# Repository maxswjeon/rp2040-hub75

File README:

# RP2040 HUB75 Panel Library

This is a HUB75 Panel Library, with PIO and DMA support and Virtual Screen with Chainning

## Virtual Screen

> **Info**
>
> Currently, constructing panels with different sizes are not supported yet.

### Configuration

Virtual Screen is constructed with same `Panel` class. The constructor should be called with those informations.

- Physical Panel Width
- Physical Panel Height
- Physical Panel Count
- `PanelConfig` array

**Important**
The order of the `PanelConfig` info should follow the wire, from the closest to the RP2040 to the end.

#### Examples

**Example 1**

```
------------------------      ------------------------
|                      |      |                      |
|                      | ---- |                      |
|                    . |      |                    . |
------------------------      ------------------------
            |
------------------------      ------------------------
| .                    |      | .                    |
|                      | ---- |                      | ---
|                      |      |                      |
------------------------      ------------------------
```

```json
[
  {
    "rotation": 0,
    "next_position": "LEFT"
  },
  {
    "rotation": 0,
    "next_position": "UP"
  },
  {
    "rotation": 180,
    "next_position": "RIGHT"
  },
  {
    "rotation": 180,
    "next_position": "NONE"
  }
]
```

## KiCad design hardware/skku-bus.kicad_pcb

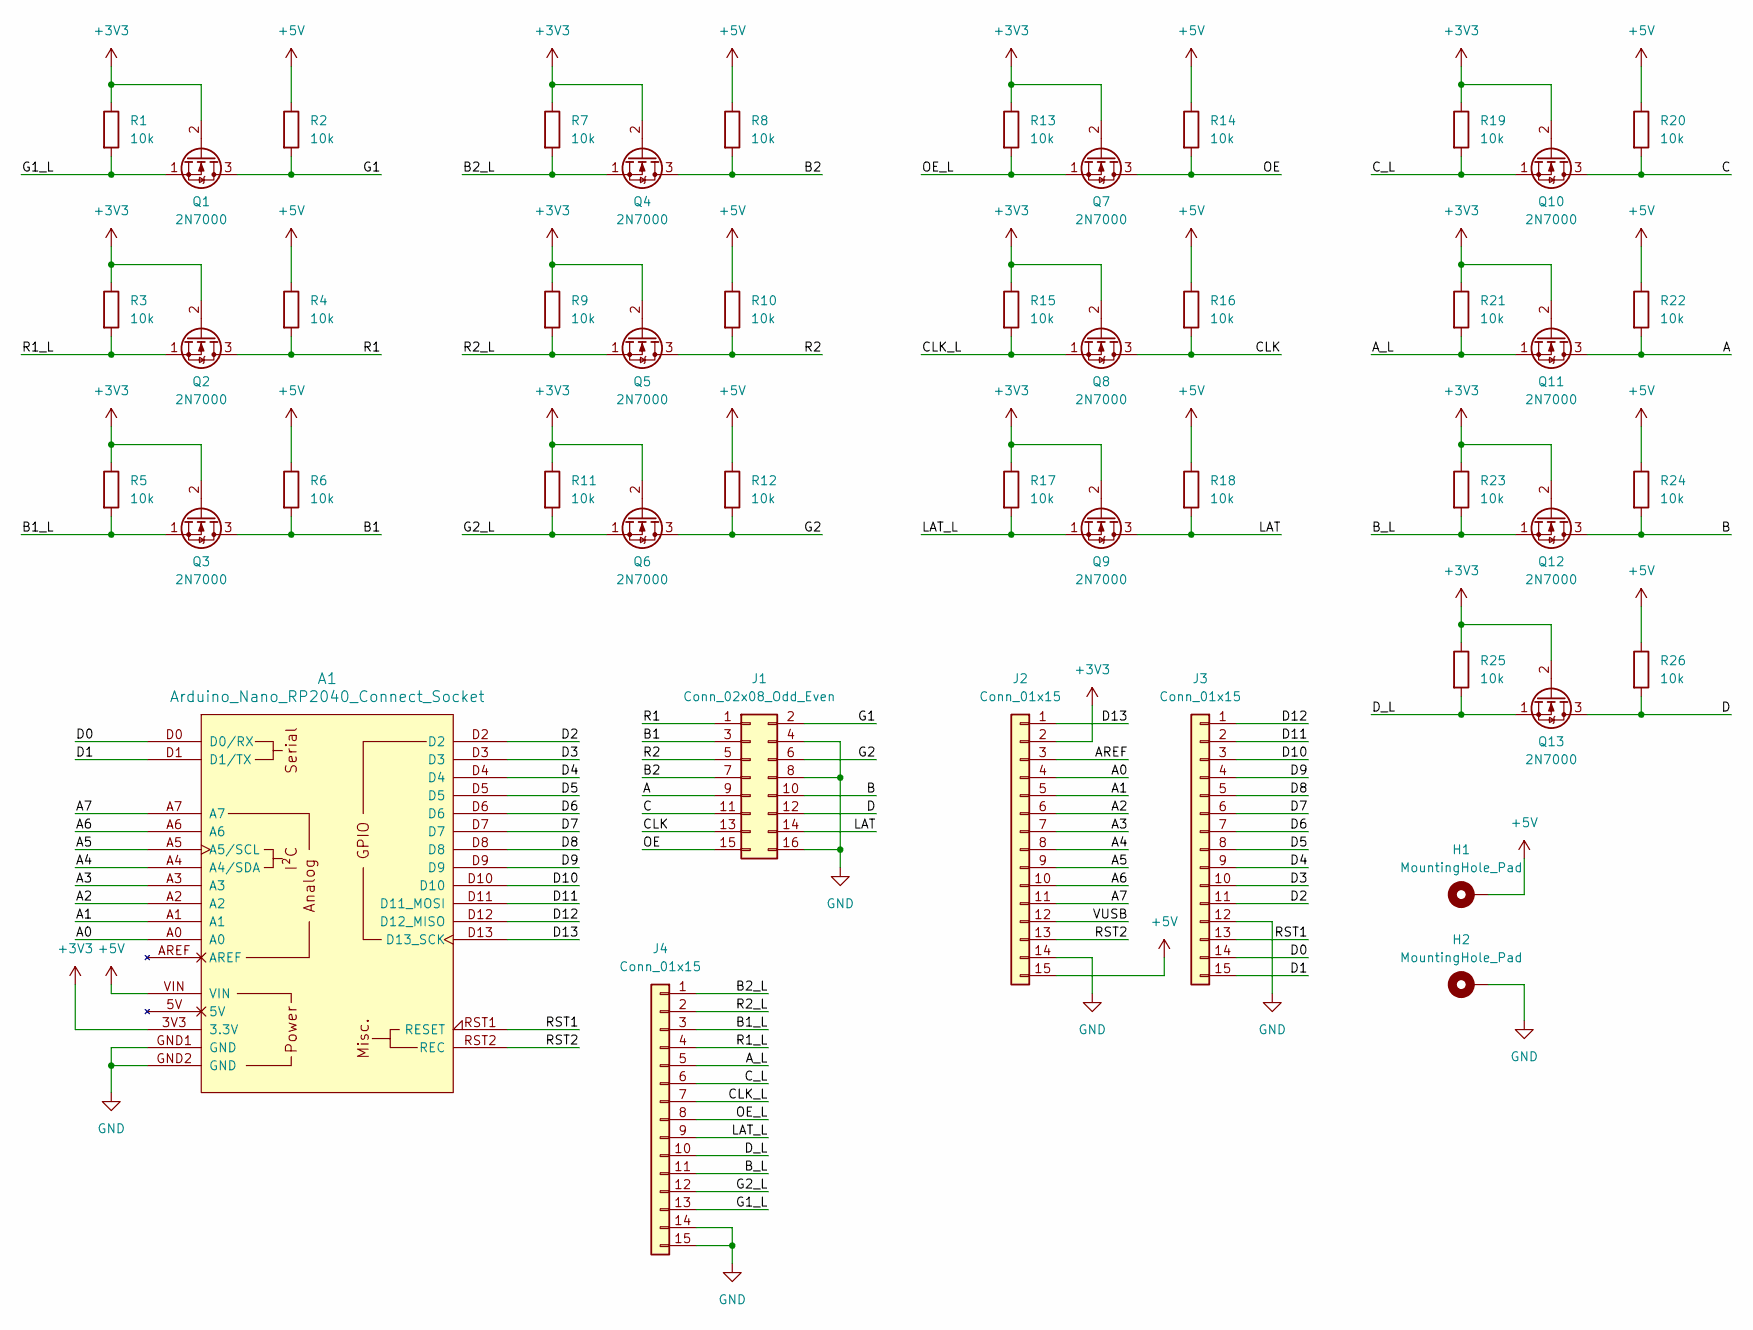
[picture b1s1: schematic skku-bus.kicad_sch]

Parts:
A1: Arduino_Nano_RP2040_Connect_Socket; Arduino_Nano_Every_Socket
H1, H2: MountingHole_Pad; MountingHole_3.2mm_M3_DIN965_Pad_TopBottom
J1: Conn_02x08_Odd_Even; IDC-Header_2x08_P2.54mm_Vertical
J2, J3: Conn_01x15; PinSocket_1x15_P2.54mm_Vertical
J4: Conn_01x15; PinHeader_1x15_P2.54mm_Vertical
Q1, Q2, Q3, Q4, Q5, Q6, Q7, Q8, Q9, Q10, Q11, Q12, Q13: 2N7000; TO-92_Inline
R1, R2, R3, R4, R5, R6, R7, R8, R9, R10, R11, R12, R13, R14, R15, R16, R17, R18, R19, R20, R21, R22, R23, R24, R25, R26: 10k; R_1206_3216Metric_Pad1.30x1.75mm_HandSolder

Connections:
+3V3: A1.3V3 (3.3V), J2.2, Q1.2 (G), Q2.2 (G), Q3.2 (G), Q4.2 (G), Q5.2 (G), Q6.2 (G), Q7.2 (G), Q8.2 (G), Q9.2 (G), Q10.2 (G), Q11.2 (G), Q12.2 (G), Q13.2 (G), R1.1, R3.1, R5.1, R7.1, R9.1, R11.1, R13.1, R15.1, R17.1, R19.1, R21.1, R23.1, R25.1
+5V: A1.VIN, H1.1, J2.15, R2.1, R4.1, R6.1, R8.1, R10.1, R12.1, R14.1, R16.1, R18.1, R20.1, R22.1, R24.1, R26.1
/A: J1.9, Q11.3 (D), R22.2
/A0: A1.A0, J2.4
/A1: A1.A1, J2.5
/A2: A1.A2, J2.6
/A3: A1.A3, J2.7
/A4: A1.A4 (A4/SDA), J2.8
/A5: A1.A5 (A5/SCL), J2.9
/A6: A1.A6, J2.10
/A7: A1.A7, J2.11
/AREF: J2.3
/A_L: J4.5, Q11.1 (S), R21.2
/B: J1.10, Q12.3 (D), R24.2
/B1: J1.3, Q3.3 (D), R6.2
/B1_L: J4.3, Q3.1 (S), R5.2
/B2: J1.7, Q4.3 (D), R8.2
/B2_L: J4.1, Q4.1 (S), R7.2
/B_L: J4.11, Q12.1 (S), R23.2
/C: J1.11, Q10.3 (D), R20.2
/CLK: J1.13, Q8.3 (D), R16.2
/CLK_L: J4.7, Q8.1 (S), R15.2
/C_L: J4.6, Q10.1 (S), R19.2
/D: J1.12, Q13.3 (D), R26.2
/D0: A1.D0 (D0/RX), J3.14
/D1: A1.D1 (D1/TX), J3.15
/D2: A1.D2, J3.11
/D3: A1.D3, J3.10
/D4: A1.D4, J3.9
/D5: A1.D5, J3.8
/D6: A1.D6, J3.7
/D7: A1.D7, J3.6
/D8: A1.D8, J3.5
/D9: A1.D9, J3.4
/D10: A1.D10, J3.3
/D11: A1.D11 (D11_MOSI), J3.2
/D12: A1.D12 (D12_MISO), J3.1
/D13: A1.D13 (D13_SCK), J2.1
/D_L: J4.10, Q13.1 (S), R25.2
/G1: J1.2, Q1.3 (D), R2.2
/G1_L: J4.13, Q1.1 (S), R1.2
/G2: J1.6, Q6.3 (D), R12.2
/G2_L: J4.12, Q6.1 (S), R11.2
/LAT: J1.14, Q9.3 (D), R18.2
/LAT_L: J4.9, Q9.1 (S), R17.2
/OE: J1.15, Q7.3 (D), R14.2
/OE_L: J4.8, Q7.1 (S), R13.2
/R1: J1.1, Q2.3 (D), R4.2
/R1_L: J4.4, Q2.1 (S), R3.2
/R2: J1.5, Q5.3 (D), R10.2
/R2_L: J4.2, Q5.1 (S), R9.2
/RST1: A1.RST1 (RESET), J3.13
/RST2: A1.RST2 (REC), J2.13
/VUSB: J2.12
GND: A1.GND1 (GND), A1.GND2 (GND), H2.1, J1.4, J1.8, J1.16, J2.14, J3.12, J4.14, J4.15

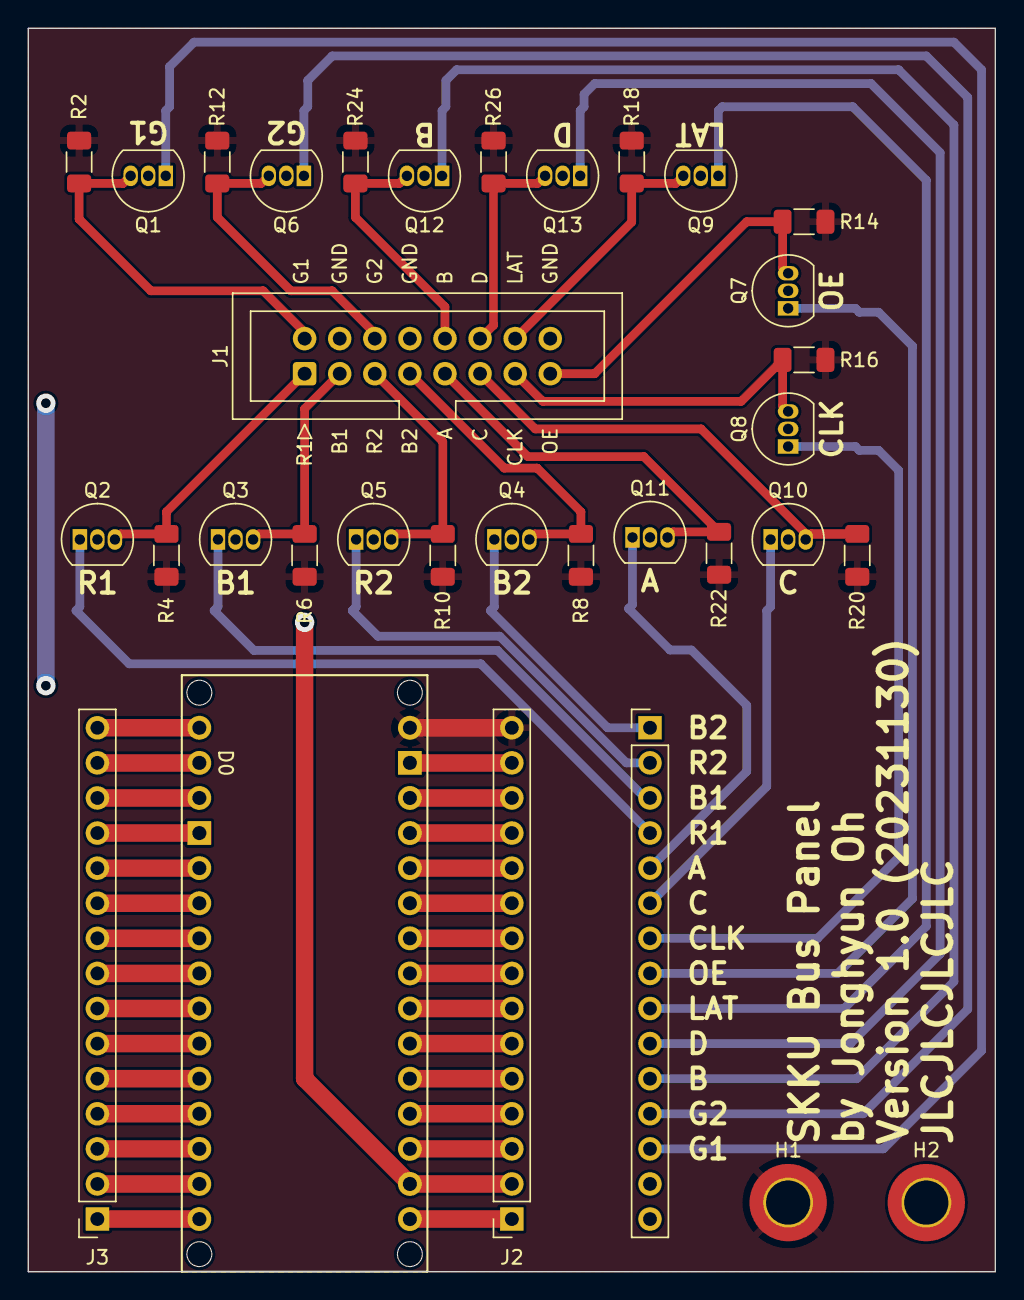
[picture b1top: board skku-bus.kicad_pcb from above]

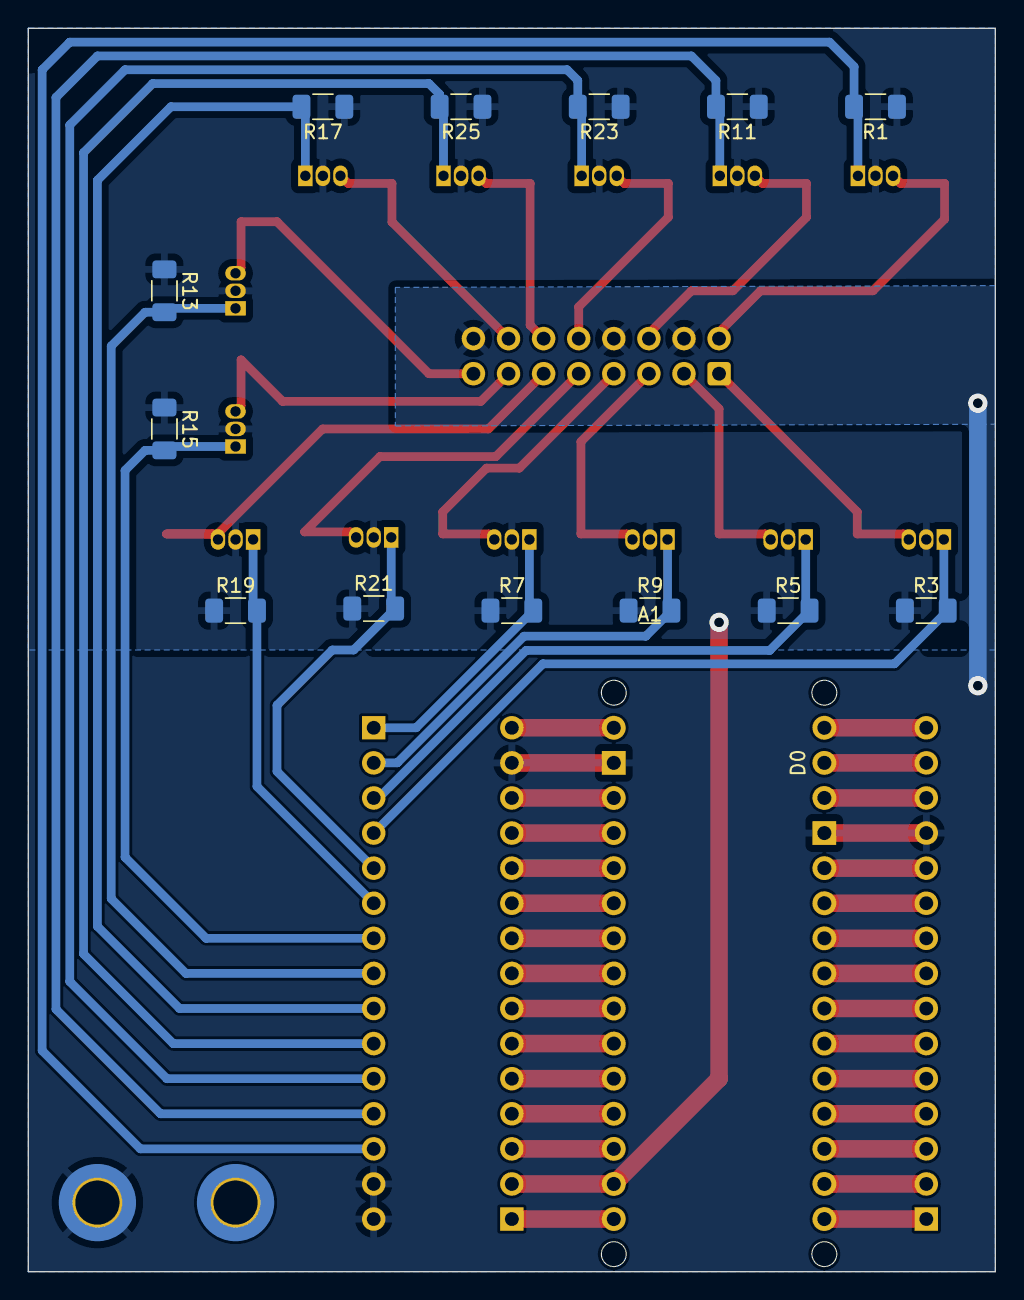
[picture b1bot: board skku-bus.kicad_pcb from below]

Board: 2 copper layers, 70.0 x 90.0 mm, 46 parts (13 on the bottom side), 53 nets.

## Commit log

2023-12-06 chore: initialize repository
2023-12-07 wip: what were I doing?
2023-12-07 feat: basic test
2023-12-08 feat: bluescreen
